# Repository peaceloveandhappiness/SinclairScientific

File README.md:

# Sinclair Scientific

This is a recreation of the original 1974 Scientific Calculator, the first affordable calculator with more than just + - ÷ ×.

Hewlett Packard had released it’s first “scientific” calculator two years earlier, and despite it costing literally as much as a fairly nice used car, it was a very successful product. Texas Instruments, on the other hand, had a widely available “four function” chip that was the heart of every cheap digital calculator, but was limited to adding, subtracting, multiplying and dividing, with limited precision.

Enter Clive Sinclair and Nigel Searle, who figured out how to use the ultra-meager 320 bytes of instruction space on that TI device to implement sine, asin, cos, acos, tan, atan, log, and antilog, in scientific notation! A feat of hacking that’s mystifying even now.

We have recreated this hallowed machine using an emulator of the TI chip, running the original instructions, at the original speed. It has lots of quirks and issues, some of which are described in this manual, some of which we had fun exploring. Far from diminishing it, these idiosyncrasies, in reality, highlight the amazing achievement that this device represents.

Enjoy!

## Inspiration

This work was inspired by and largely based upon [ArduinoEnigma's similar project](https://gitlab.com/arduinoenigma/ArduinoNanoSinclairScientificCalculator), which was inspired by [Ken Shirriff's Sinclair Scientific Calculator Simulator](http://righto.com/sinclair). The hardware design is based upon [Adafruit's Feather M0](https://github.com/adafruit/Adafruit-Feather-M0-Basic-Proto-PCB), as well as [ArduinoEnigma's hardware designs](https://hackaday.io/project/91895-sinclair-scientific-calculator-emulator). The firmware used in this project is based on [ArduinoEnigma's SinclairScientific7 code](https://gitlab.com/arduinoenigma/ArduinoNanoSinclairScientificCalculator/tree/master/SinclairScientific7) and [Adafruit's SAMD toolchain](https://github.com/adafruit/ArduinoCore-samd).

* [Ken Shirriff's Simulator](http://files.righto.com/calculator/sinclair_scientific_simulator.html)
* [ArduinoEnigma's Arduino Code](https://github.com/arduinoenigma/ArduinoNanoSinclairScientificCalculator)
* [ArduinoEnigma's Hackster Guide](https://www.hackster.io/arduinoenigma/sinclair-scientific-calculator-emulator-a11dba)
* [ArduinoEnigma's Hackaday Guide](https://hackaday.io/project/91895-sinclair-scientific-calculator-emulator)
* [ArduinoEnigma's Tindie Page](https://www.tindie.com/products/ArduinoEnigma/sinclair-scientific-calculator-emulator/)
* [Adafruit's Feather M0](https://github.com/adafruit/Adafruit-Feather-M0-Basic-Proto-PCB)

## Credits

* Thank you Joerg Woerner of [Datamath Calculator Museum](www.datamath.org/) for finding and scanning the original [Sinclair Scientific Operating Manual](www.datamath.net/Manuals_Others/Sinclair_Scientific_GB.pdf).
* Thank you [Katherine Wasserman](www.wass.net/) for finding the original [Sinclair Scientific Assembly Manual](www.wass.net/manuals/Sinclair%20Scientific%20Assembly.pdf)
* Thank you [ArduinoEnigma](www.arduinoenigma.blogspot.com) for starting the project and making the previous iterations. Awesome work!
* Thank you [Ken Shirriff](www.righto.com) for your immense talents and hard work, not only on this emulator but on lots of interesting stuff.
* Thank you [Adafruit](www.adafruit.com) for all of your incredible open source work.

## Additional Information

* [Wikipedia Page for the Sinclair Scientific](https://en.wikipedia.org/wiki/Sinclair_Scientific)
* [Historical Info about the Sinclair Scientific](http://rk.nvg.ntnu.no/sinclair/calculators/scientific.htm)
* [Technical Info about the Sinclair Scientific](http://www.vintagecalculators.com/html/scientific_-_giant_scientific.html)
* [Sinclair Scientific Operating Manual](http://www.datamath.net/Manuals_Others/Sinclair_Scientific_GB.pdf)
* [Sinclair Scientific Assembly Manual](http://www.wass.net/manuals/Sinclair%20Scientific%20Assembly.pdf)

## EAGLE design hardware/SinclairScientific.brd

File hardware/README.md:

# Sinclair Scientific Hardware

## Revision History

### v1A

* Initial revision, based on [ArduinoEnigma's design](https://cdn.hackaday.io/files/918953931635680/V5%20Schematic.png)

### v1B

* Replaced Arduino NANO MCU with one used by Adafruit Feather M0 (SAMD21G18)
* Replaced alkaline batteries with LiPo battery
* Added LiPo battery charging circuit
* Changed LED resistor values to work with 3.3V
* Changed 7-segment displays to mount on a daughter board to allow them to be flush mounted with the faceplate
* Swapped existing tactile buttons for ones that can be used with button caps
* Swapped existing ON/OFF switch for more comfortable one
* Added charging LED that can be seen by user
* Moved LED segments [B, E] to [D0, D1] pins to allow button input lines to use [D8, D9] exclusively

### v1C

* Fixed footprint for flash memory IC
* Changed button spacing to match original sinclair dimensions
* Replaced power switch with SMT device

### Future Changes

* Consider using LED or 7-segment display driver
  * [MAX6954](https://www.maximintegrated.com/en/app-notes/index.mvp/id/3210)
  * [MAX6957](https://www.maximintegrated.com/en/products/power/display-power-control/MAX6957.html)
  * [MAX7301](https://www.maximintegrated.com/en/products/interface/controllers-expanders/MAX7301.html)
  * Maxim has many other parts that may work better

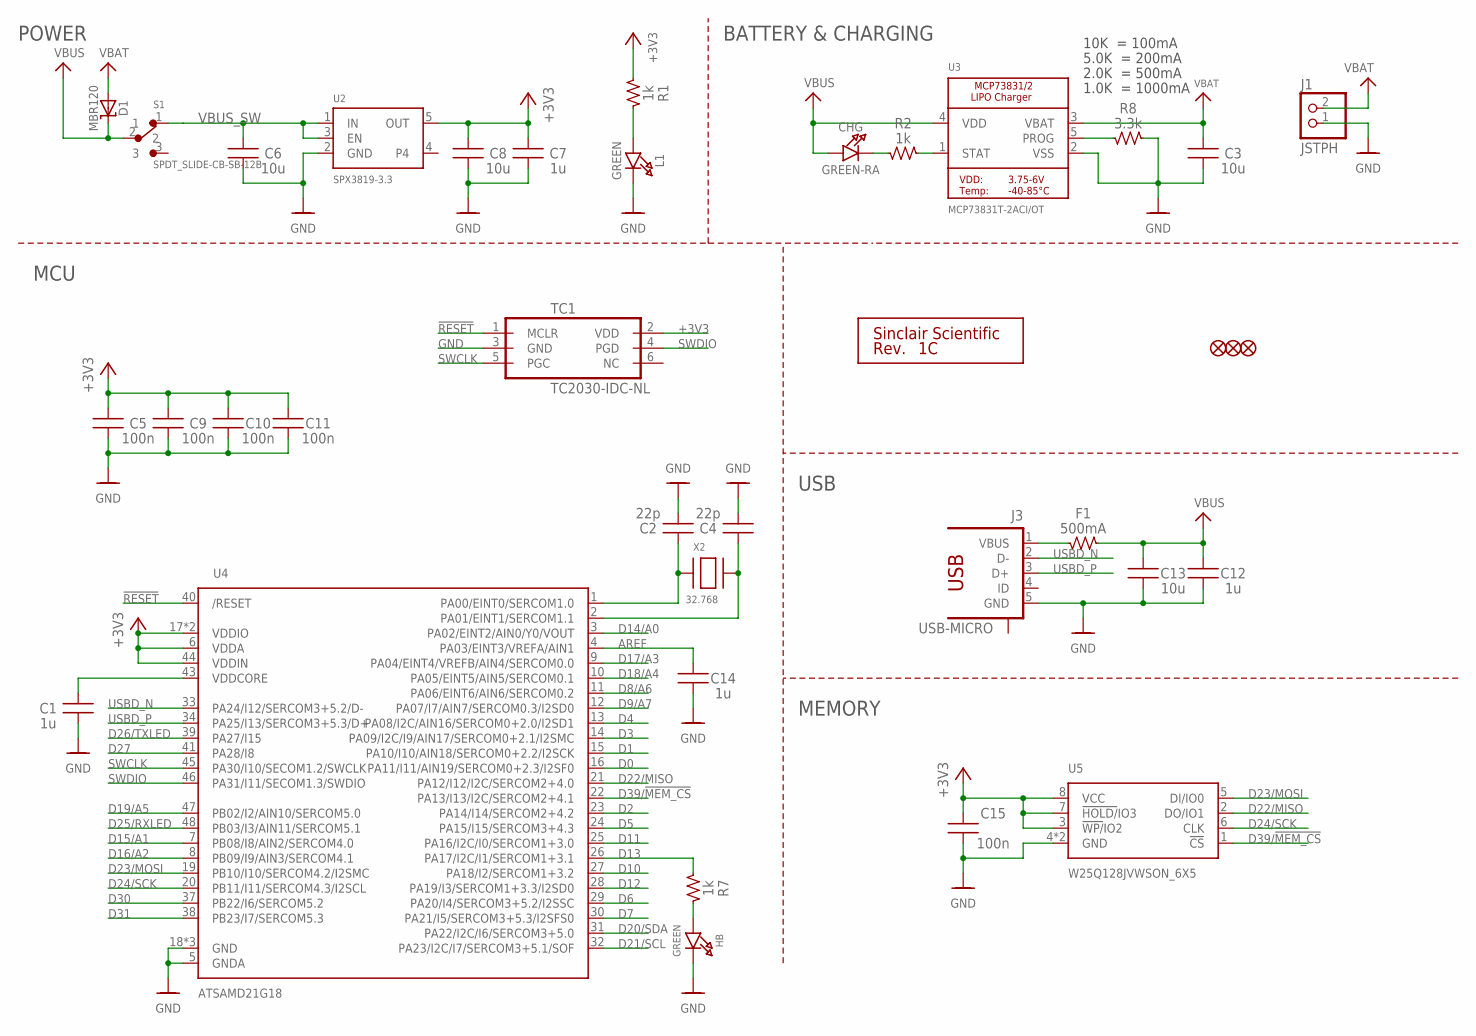
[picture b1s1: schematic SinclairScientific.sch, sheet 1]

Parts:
C1, C7, C12, C14: 1u; C0603; MPN C1608X7R1C105M080AC
C2, C4: 22p; C0603; MPN GQM1875C2E220JB12D
C3, C6, C8, C13: 10u; C0805; MPN GRM21BR61C106KE15K
C5, C9, C10, C11, C15: 100n; C0603; MPN 06035C104K4Z4A
CHG: GREEN-RA; CHIPLED_0805_NOOUTLINE; MPN LTST-S220KGKT
D1: MBR120; SOD-123; MPN MBR120VLSFT1G
F1: 500mA; R0805; MPN 0ZCK0050FF2E
FID1, FID2, FID3: FIDUCIAL""; FIDUCIAL_1MM
HB: GREEN; CHIPLED_0805_NOOUTLINE; MPN LTST-C170GKT
J1: JSTPH; JSTPH2; MPN S2B-PH-SM4-TB(LF)(SN)
J3: USB-MICRO; USB-10118192-0001LF
L1: GREEN; CHIPLED_0805_NOOUTLINE; MPN LTST-C170GKT
R1, R2, R7: 1k; R0603; MPN RC0603FR-071KL
R8: 3.3k; R0603; MPN RC0603FR-073K3L
S1: SPDT_SLIDE-CB-SB-12B; CL-SB-12B; MPN CL-SB-12B-01T
SILK-QC: SILK_QC
TC1: TC2030-IDC-NL
U2: SPX3819-3.3; SOT23-5; MPN SPX3819M5-L-3-3/TR
U3: MCP73831T-2ACI/OT; SOT23-5; MPN MCP73831T-2ACI/OT
U4: ATSAMD21G18; TQFP48_7MM; MPN ATSAMD21G18A-AUT
U5: W25Q128JVWSON_6X5; SON127P600X500X80-9N; MPN W25Q128JVPIM
X2: 32.768; XTAL3215; MPN ECS-.327-12.5-34B-TR

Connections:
!RESET: TC1.1 (MCLR), U4.40 (/RESET)
+3V3: C5.1, C7.1, C8.1, C9.1, C10.1, C11.1, C15.1, R1.1, TC1.2 (VDD), U2.5 (OUT), U4.6 (VDDA), U4.17 (VDDIO), U4.36 (VDDIO), U4.44 (VDDIN), U5.3 (!WP/!IO2), U5.7 (!HOLD/!IO3), U5.8 (VCC); also elsewhere on the board
AREF: C14.1, U4.4 (PA03/EINT3/VREFA/AIN1)
D0: U4.16 (PA11/I11/AIN19/SERCOM0+2.3/I2SF0); also elsewhere on the board
D1: U4.15 (PA10/I10/AIN18/SERCOM0+2.2/I2SCK); also elsewhere on the board
D2: U4.23 (PA14/I14/SERCOM2+4.2); also elsewhere on the board
D3: U4.14 (PA09/I2C/I9/AIN17/SERCOM0+2.1/I2SMC); also elsewhere on the board
D4: U4.13 (PA08/I2C/AIN16/SERCOM0+2.0/I2SD1); also elsewhere on the board
D5: U4.24 (PA15/I15/SERCOM3+4.3); also elsewhere on the board
D6: U4.29 (PA20/I4/SERCOM3+5.2/I2SSC); also elsewhere on the board
D7: U4.30 (PA21/I5/SERCOM3+5.3/I2SFS0); also elsewhere on the board
D8/A6: U4.11 (PA06/EINT6/AIN6/SERCOM0.2); also elsewhere on the board
D9/A7: U4.12 (PA07/I7/AIN7/SERCOM0.3/I2SD0); also elsewhere on the board
D10: U4.27 (PA18/I2/SERCOM1+3.2); also elsewhere on the board
D11: U4.25 (PA16/I2C/I0/SERCOM1+3.0); also elsewhere on the board
D12: U4.28 (PA19/I3/SERCOM1+3.3/I2SD0); also elsewhere on the board
D13: R7.1, U4.26 (PA17/I2C/I1/SERCOM1+3.1)
D14/A0: U4.3 (PA02/EINT2/AIN0/Y0/VOUT); also elsewhere on the board
D15/A1: U4.7 (PB08/I8/AIN2/SERCOM4.0); also elsewhere on the board
D16/A2: U4.8 (PB09/I9/AIN3/SERCOM4.1); also elsewhere on the board
D17/A3: U4.9 (PA04/EINT4/VREFB/AIN4/SERCOM0.0); also elsewhere on the board
D18/A4: U4.10 (PA05/EINT5/AIN5/SERCOM0.1); also elsewhere on the board
D19/A5: U4.47 (PB02/I2/AIN10/SERCOM5.0); also elsewhere on the board
D20/SDA: U4.31 (PA22/I2C/I6/SERCOM3+5.0)
D21/SCL: U4.32 (PA23/I2C/I7/SERCOM3+5.1/SOF)
D22/MISO: U4.21 (PA12/I12/I2C/SERCOM2+4.0), U5.2 (DO/IO1)
D23/MOSI: U4.19 (PB10/I10/SERCOM4.2/I2SMC), U5.5 (DI/IO0)
D24/SCK: U4.20 (PB11/I11/SERCOM4.3/I2SCL), U5.6 (CLK)
D25/RXLED: U4.48 (PB03/I3/AIN11/SERCOM5.1)
D26/TXLED: U4.39 (PA27/I15)
D27: U4.41 (PA28/I8)
D30: U4.37 (PB22/I6/SERCOM5.2)
D31: U4.38 (PB23/I7/SERCOM5.3)
D39/!MEM_CS: U4.22 (PA13/I13/I2C/SERCOM2+4.1), U5.1 (!CS)
EXTAL32: C2.1, U4.1 (PA00/EINT0/SERCOM1.0), X2.P$1
GND: C1.2, C2.2, C3.2, C4.2, C5.2, C6.2, C7.2, C8.2, C9.2, C10.2, C11.2, C12.2, C13.2, C14.2, C15.2, HB.C, J1.1, J3.5 (GND), L1.C, R8.2, TC1.3 (GND), U2.2 (GND), U3.2 (VSS), U4.5 (GNDA), U4.18 (GND), U4.35 (GND), U4.42 (GND), U5.4 (GND), U5.9 (GND); also elsewhere on the board
unnamed: CHG.C, R2.1
unnamed: HB.A, R7.2
unnamed: R2.2, U3.1 (STAT)
unnamed: R8.1, U3.5 (PROG)
unnamed: L1.A, R1.2
unnamed: F1.1, J3.1 (VBUS)
SWCLK: TC1.5 (PGC), U4.45 (PA30/I10/SECOM1.2/SWCLK)
SWDIO: TC1.4 (PGD), U4.46 (PA31/I11/SECOM1.3/SWDIO)
USBD_N: J3.2 (D-), U4.33 (PA24/I12/SERCOM3+5.2/D-)
USBD_P: J3.3 (D+), U4.34 (PA25/I13/SERCOM3+5.3/D+)
VBAT: C3.1, D1.A, J1.2, U3.3 (VBAT)
VBUS: C12.1, C13.1, CHG.A, D1.C, F1.2, S1.2, U3.4 (VDD)
VBUS_SW: C6.1, S1.1, U2.1 (IN), U2.3 (EN)
VDDCORE: C1.1, U4.43 (VDDCORE)
XTAL32: C4.1, U4.2 (PA01/EINT1/SERCOM1.1), X2.P$2

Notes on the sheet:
POWER
10K = 100mA
5.0K = 200mA
2.0K = 500mA
1.0K = 1000mA
BATTERY & CHARGING
USB
MCU
MEMORY

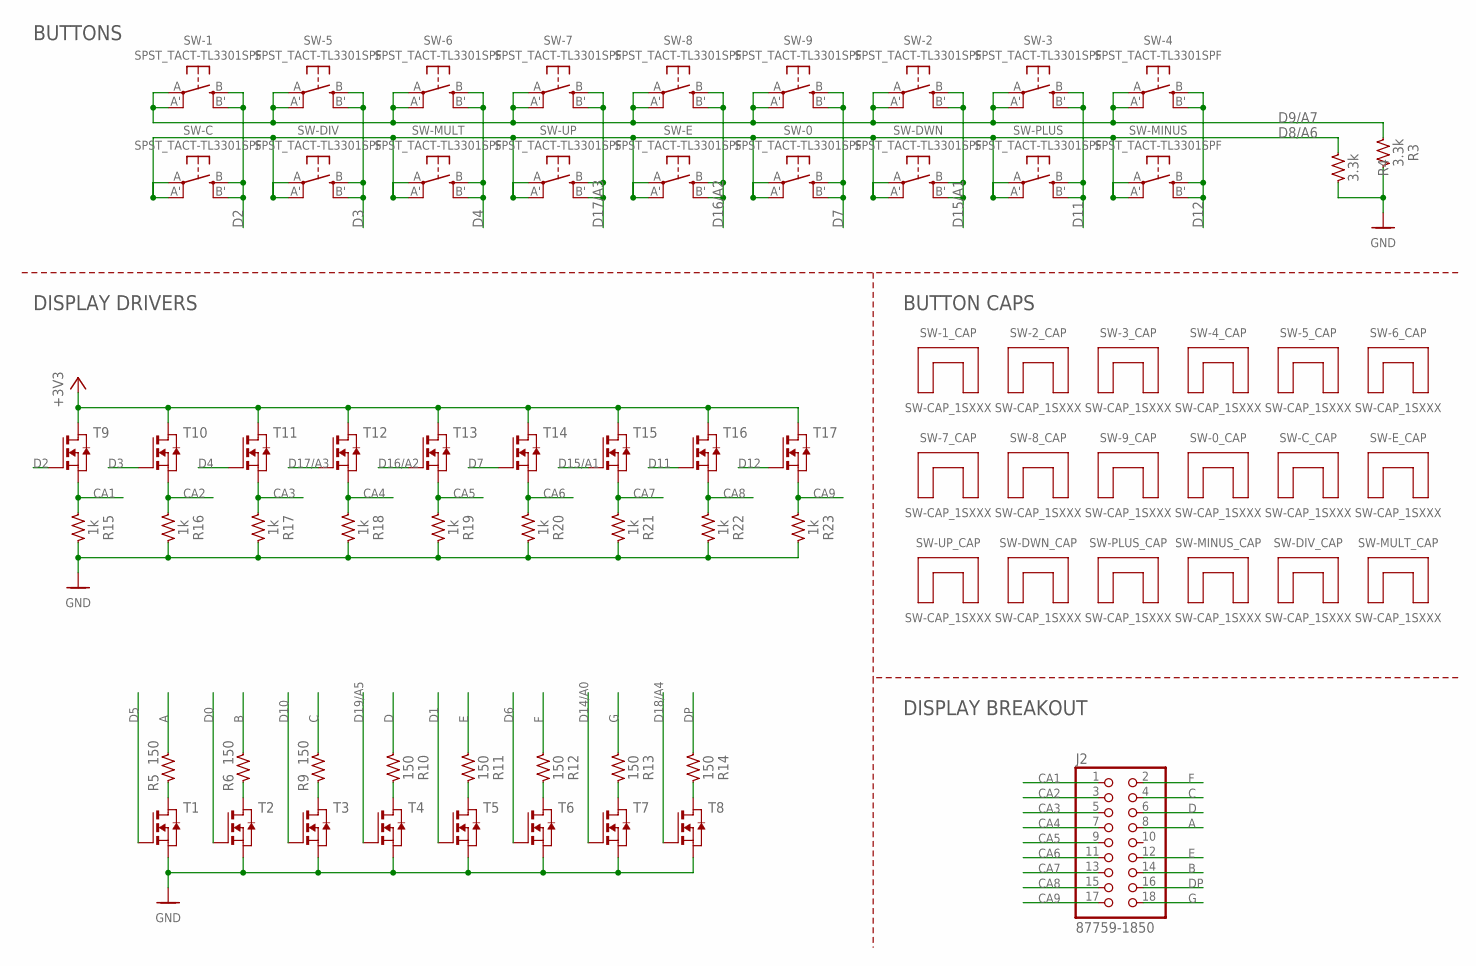
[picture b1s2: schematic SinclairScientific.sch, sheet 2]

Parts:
J2: 87759-1850; 2X09-2MM-SMD; MPN 87759-1850
R3, R4: 3.3k; R0603; MPN RC0603FR-073K3L
R5, R6, R9, R10, R11, R12, R13, R14: 150; R0603; MPN RC0603FR-07150RL
R15, R16, R17, R18, R19, R20, R21, R22, R23: 1k; R0603; MPN RC0603FR-071KL
SW-0, SW-2, SW-3, SW-4, SW-5, SW-6, SW-7, SW-8, SW-9: SPST_TACT-TL3301SPF; TACT_6X6
SW-0_CAP, SW-1_CAP, SW-2_CAP, SW-3_CAP, SW-4_CAP, SW-5_CAP, SW-6_CAP, SW-7_CAP, SW-8_CAP, SW-9_CAP: SW-CAP_1SXXX; SW-CAP_1SWXXX
SW-1: SPST_TACT-TL3301SPF; TACT_6X6; MPN TL3301SPF260QG
SW-C: SPST_TACT-TL3301SPF; TACT_6X6
SW-C_CAP: SW-CAP_1SXXX; SW-CAP_1SWXXX
SW-DIV: SPST_TACT-TL3301SPF; TACT_6X6
SW-DIV_CAP: SW-CAP_1SXXX; SW-CAP_1SWXXX
SW-DWN: SPST_TACT-TL3301SPF; TACT_6X6
SW-DWN_CAP: SW-CAP_1SXXX; SW-CAP_1SWXXX
SW-E: SPST_TACT-TL3301SPF; TACT_6X6
SW-E_CAP: SW-CAP_1SXXX; SW-CAP_1SWXXX
SW-MINUS: SPST_TACT-TL3301SPF; TACT_6X6
SW-MINUS_CAP: SW-CAP_1SXXX; SW-CAP_1SWXXX
SW-MULT: SPST_TACT-TL3301SPF; TACT_6X6
SW-MULT_CAP: SW-CAP_1SXXX; SW-CAP_1SWXXX
SW-PLUS: SPST_TACT-TL3301SPF; TACT_6X6
SW-PLUS_CAP: SW-CAP_1SXXX; SW-CAP_1SWXXX
SW-UP: SPST_TACT-TL3301SPF; TACT_6X6
SW-UP_CAP: SW-CAP_1SXXX; SW-CAP_1SWXXX
T1, T2, T3, T4, T5, T6, T7, T8, T10, T11, T12, T13, T14, T15, T16, T17: NMOSSOT23-FDV303N; SOT-23
T9: NMOSSOT23-FDV303N; SOT-23; MPN FDV303N

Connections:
+3V3: T9.1 (D), T10.1 (D), T11.1 (D), T12.1 (D), T13.1 (D), T14.1 (D), T15.1 (D), T16.1 (D), T17.1 (D); also elsewhere on the board
A: J2.8, R5.1
B: J2.14, R6.1
C: J2.4, R9.1
CA1: J2.1, R15.1, T9.2 (S)
CA2: J2.3, R16.1, T10.2 (S)
CA3: J2.5, R17.1, T11.2 (S)
CA4: J2.7, R18.1, T12.2 (S)
CA5: J2.9, R19.1, T13.2 (S)
CA6: J2.11, R20.1, T14.2 (S)
CA7: J2.13, R21.1, T15.2 (S)
CA8: J2.15, R22.1, T16.2 (S)
CA9: J2.17, R23.1, T17.2 (S)
D: J2.6, R10.1
D0: T2.3 (G); also elsewhere on the board
D1: T5.3 (G); also elsewhere on the board
D2: SW-1.B (S), SW-1.B' (S1), SW-C.B (S), SW-C.B' (S1), T9.3 (G); also elsewhere on the board
D3: SW-5.B (S), SW-5.B' (S1), SW-DIV.B (S), SW-DIV.B' (S1), T10.3 (G); also elsewhere on the board
D4: SW-6.B (S), SW-6.B' (S1), SW-MULT.B (S), SW-MULT.B' (S1), T11.3 (G); also elsewhere on the board
D5: T1.3 (G); also elsewhere on the board
D6: T6.3 (G); also elsewhere on the board
D7: SW-0.B (S), SW-0.B' (S1), SW-9.B (S), SW-9.B' (S1), T14.3 (G); also elsewhere on the board
D8/A6: R4.1, SW-0.A, SW-0.A' (P1), SW-C.A, SW-C.A' (P1), SW-DIV.A, SW-DIV.A' (P1), SW-DWN.A, SW-DWN.A' (P1), SW-E.A, SW-E.A' (P1), SW-MINUS.A, SW-MINUS.A' (P1), SW-MULT.A, SW-MULT.A' (P1), SW-PLUS.A, SW-PLUS.A' (P1), SW-UP.A, SW-UP.A' (P1); also elsewhere on the board
D9/A7: R3.1, SW-1.A, SW-1.A' (P1), SW-2.A, SW-2.A' (P1), SW-3.A, SW-3.A' (P1), SW-4.A, SW-4.A' (P1), SW-5.A, SW-5.A' (P1), SW-6.A, SW-6.A' (P1), SW-7.A, SW-7.A' (P1), SW-8.A, SW-8.A' (P1), SW-9.A, SW-9.A' (P1); also elsewhere on the board
D10: T3.3 (G); also elsewhere on the board
D11: SW-3.B (S), SW-3.B' (S1), SW-PLUS.B (S), SW-PLUS.B' (S1), T16.3 (G); also elsewhere on the board
D12: SW-4.B (S), SW-4.B' (S1), SW-MINUS.B (S), SW-MINUS.B' (S1), T17.3 (G); also elsewhere on the board
D14/A0: T7.3 (G); also elsewhere on the board
D15/A1: SW-2.B (S), SW-2.B' (S1), SW-DWN.B (S), SW-DWN.B' (S1), T15.3 (G); also elsewhere on the board
D16/A2: SW-8.B (S), SW-8.B' (S1), SW-E.B (S), SW-E.B' (S1), T13.3 (G); also elsewhere on the board
D17/A3: SW-7.B (S), SW-7.B' (S1), SW-UP.B (S), SW-UP.B' (S1), T12.3 (G); also elsewhere on the board
D18/A4: T8.3 (G); also elsewhere on the board
D19/A5: T4.3 (G); also elsewhere on the board
DP: J2.16, R14.1
E: J2.12, R11.1
F: J2.2, R12.1
G: J2.18, R13.1
GND: R3.2, R4.2, R15.2, R16.2, R17.2, R18.2, R19.2, R20.2, R21.2, R22.2, R23.2, T1.2 (S), T2.2 (S), T3.2 (S), T4.2 (S), T5.2 (S), T6.2 (S), T7.2 (S), T8.2 (S); also elsewhere on the board
unnamed: R5.2, T1.1 (D)
unnamed: R6.2, T2.1 (D)
unnamed: R9.2, T3.1 (D)
unnamed: R10.2, T4.1 (D)
unnamed: R11.2, T5.1 (D)
unnamed: R12.2, T6.1 (D)
unnamed: R13.2, T7.1 (D)
unnamed: R14.2, T8.1 (D)

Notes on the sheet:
BUTTONS
DISPLAY DRIVERS
DISPLAY BREAKOUT
BUTTON CAPS

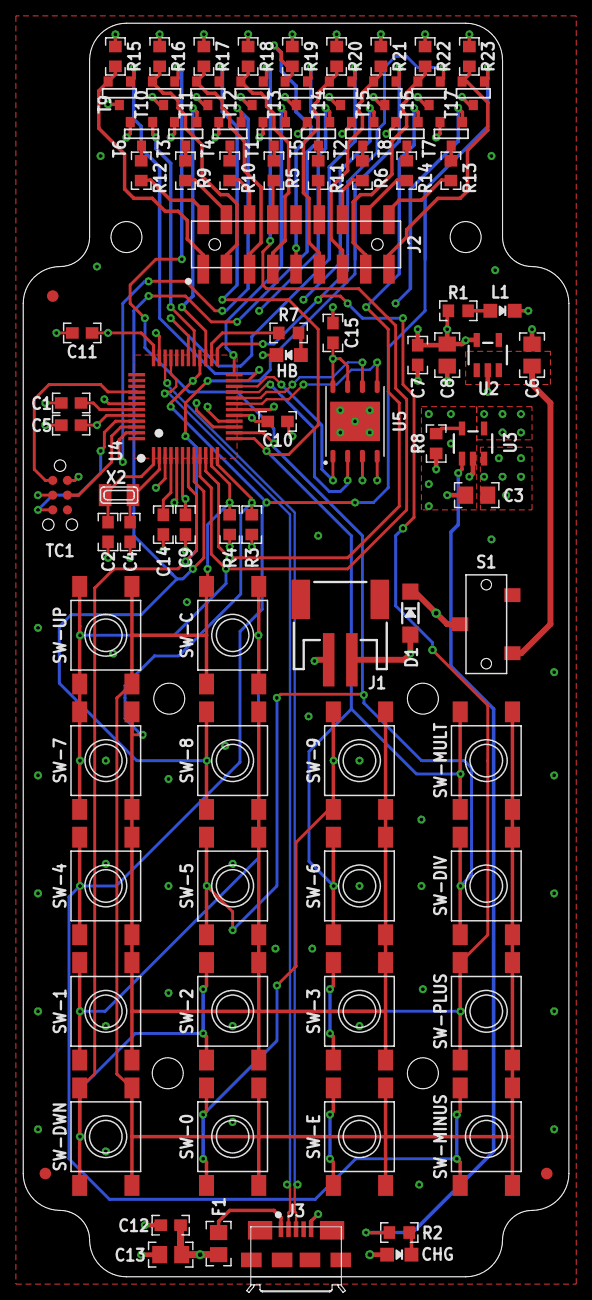
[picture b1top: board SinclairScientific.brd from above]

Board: 4 copper layers, 47.0 x 108.0 mm, 117 parts (2 on the bottom side), 69 nets.

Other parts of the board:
U$17: LOGO_PLH_2700
U$50, U$51, U$52, U$53, U$54, U$55: HOLE_3-48

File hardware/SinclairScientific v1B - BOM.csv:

Qty,DNP,Value,Parts,MFG,MPN,PN-DK,Device,Package,Description,
2,,22pF,"C2, C4",Murata Electronics North America,GQM1875C2E220JB12D,490-16699-1-ND,C-USC0603,C0603,CAP CER 22PF 250V NP0 0603,
5,,100n,"C9, C10, C11, C5, C15",AVX Corporation,06035C104K4Z4A,478-10679-1-ND,C-USC0603,C0603,CAP CER 0.1UF 50V X7R 0603,
4,,1uF,"C1, C7, C12, C14",TDK Corporation,C1608X7R1C105M080AC,445-5131-1-ND,C-USC0603,C0603,CAP CER 1UF 16V X7R 0603,
4,,10uF,"C3, C6, C8, C13",Murata Electronics North America,GRM21BR61C106KE15K,490-6473-1-ND,C-USC0805,C0805,CAP CER 10UF 16V X5R 0805,
8,,150,"R5, R6, R9, R10, R11, R12, R13, R14",Yageo,RC0603FR-07150RL,311-150HRCT-ND,R-US_R0603,R0603,RES SMD 150 OHM 1% 1/10W 0603,
12,,1k,"R1, R2, R7, R15, R16, R17, R18, R19, R20, R21, R22, R23",Yageo,RC0603FR-071KL,311-1.00KHRCT-ND,R-US_R0603,R0603,RES SMD 1K OHM 1% 1/10W 0603,
3,,3.3k,"R3, R4, R8",Yageo,RC0603FR-073K3L,311-3.30KHRCT-ND,R-US_R0603,R0603,RES SMD 3.3K OHM 1% 1/10W 0603,
1,,500mA,F1,Bel Fuse Inc.,0ZCK0050FF2E,507-1813-1-ND,R-US_R0805,R0805,PTC RESET FUSE 6V 500MA 0805,
1,,MBR120,D1,ON Semiconductor,MBR120VLSFT1G,MBR120VLSFT1GOSCT-ND,DIODE-SCHOTTKYSOD-123,SOD-123,DIODE SCHOTTKY 20V 1A SOD123FL,
2,,Green,"HB, L1",Lite-On Inc.,LTST-C170GKT,160-1179-1-ND,LED0805_NOOUTLINE,CHIPLED_0805_NOOUTLINE,LED GREEN CLEAR SMD,
1,,Green,CHG,Lite-On Inc.,LTST-S220KGKT,160-1468-1-ND,LED0805_NOOUTLINE,CHIPLED_0805_NOOUTLINE,LED GREEN CLEAR CHIP SMD R/A,
1,,32.768,X2,ECS Inc.,ECS-.327-12.5-34B-TR,XC1617CT-ND,XTAL-3.2X1.5,XTAL3215,CRYSTAL 32.7680KHZ 12.5PF SMD,
17,,,"T1, T2, T3, T4, T5, T6, T7, T8, T9, T10, T11, T12, T13, T14, T15, T16, T17",ON Semiconductor,FDV303N,FDV303NCT-ND,NMOSSOT23,SOT-23,MOSFET N-CH 25V 680MA SOT-23,x
1,,SPST_SLIDE,S1,Nidec Copal Electronics,CL-SB-12B-01T,563-1318-1-ND,SPST_SLIDE,SPST_SLIDE-CL-SB-12B,SWITCH SLIDE SPDT 200MA 12V,
18,,SPST_TACT-6X6,"SW-0, SW-1, SW-2, SW-3, SW-4, SW-5, SW-6, SW-7, SW-8, SW-9, SW-C, SW-DIV, SW-DWN, SW-E, SW-MINUS, SW-MULT, SW-PLUS, SW-UP",E-Switch,TL3301SPF260QG,EG1870CT-ND,SPST_TACT-6X6,TACT_6X6,SWITCH TACTILE SPST-NO 0.05A 12V,
1,,SPX3819-3.3,U2,"MaxLinear, Inc.",SPX3819M5-L-3-3/TR,1016-1873-1-ND,VREG_SOT23-5,SOT23-5,IC REG LINEAR 3.3V 500MA SOT23-5,
1,,MCP73831T-2ACI/OT,U3,Microchip Technology,MCP73831T-2ACI/OT,MCP73831T-2ACI/OTCT-ND,MCP73831/2,SOT23-5,IC CONTROLLR LI-ION 4.2V SOT23-5,
1,,W25Q128JVSO,U5,Winbond Electronics,W25Q128JVPIM,W25Q128JVPIMCT-ND,W25Q128JVSO,SON127P800X600X80-9N,IC FLASH 128M SPI 133MHZ 8WSON,
1,,ATSAMD21G18,U4,Microchip Technology,ATSAMD21G18A,ATSAMD21G18A-AFTCT-ND,ATSAMD21J_QFP,TQFP48_7MM,IC MCU 32BIT 256KB FLASH 48TQFP,
1,,USB-MICRO,J3,Amphenol,10118192-0001LF,609-4613-1-ND,USB-MICRO,USB-10118192-0001LF,CONN USB MICRO B RECPT SMT R/A,
1,,JSTPH,J1,JST Sales America Inc.,S2B-PH-SM4-TB(LF)(SN),455-1749-1-ND,CON_JST_PH_2PIN,JSTPH2,CONN HEADER PH SIDE 2POS 2MM SMD,
1,,,J2,Molex Connector Corporation,87759-1850,WM18656-ND ,PINHD-2X9-2MM-SMD,2X09-2MM-SMD,CONN HEADER 18POS 2MM VERT SMD,
1,DNP,TC2030-IDC-NL,TC1,Tag-Connect,TC2030-IDC,,TC2030-IDC-NL,TC2030-IDC-NL,Tag-Connect In Circuit Programming & Debug Cable 6 Pin,

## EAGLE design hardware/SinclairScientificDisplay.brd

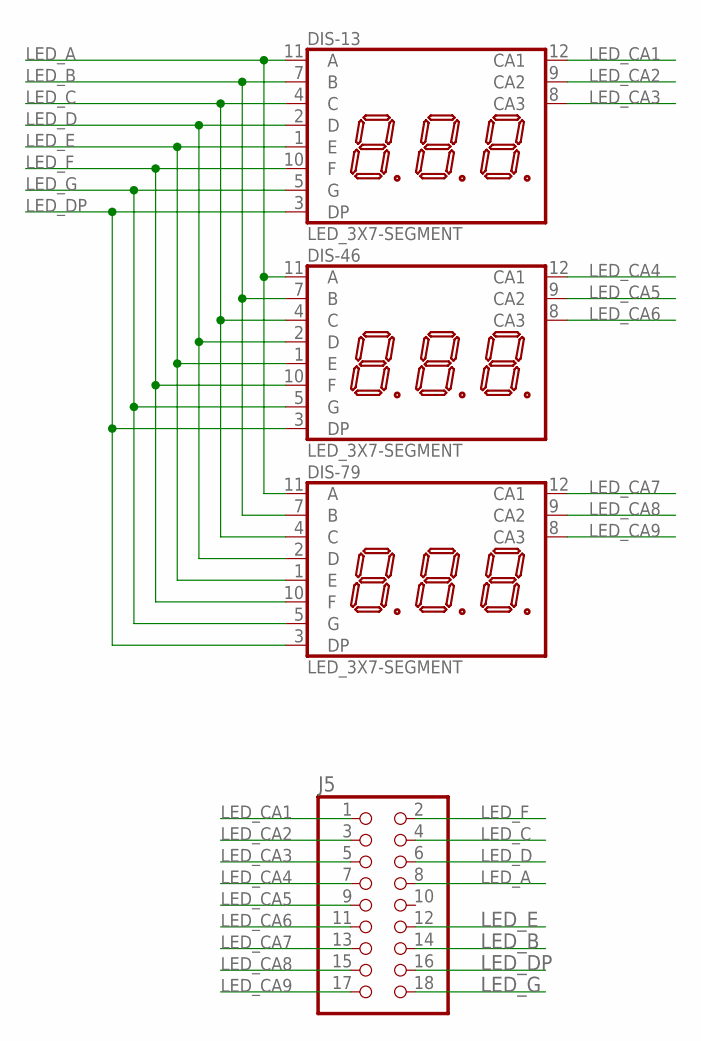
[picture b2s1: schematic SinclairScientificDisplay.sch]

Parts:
DIS-13, DIS-46, DIS-79: LED_3X7-SEGMENT; 2352B
J5: PINHD-2X9-2MM; 2X09-2MM

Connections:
LED_A: DIS-13.11 (A), DIS-46.11 (A), DIS-79.11 (A), J5.8
LED_B: DIS-13.7 (B), DIS-46.7 (B), DIS-79.7 (B), J5.14
LED_C: DIS-13.4 (C), DIS-46.4 (C), DIS-79.4 (C), J5.4
LED_CA1: DIS-13.12 (CA1), J5.1
LED_CA2: DIS-13.9 (CA2), J5.3
LED_CA3: DIS-13.8 (CA3), J5.5
LED_CA4: DIS-46.12 (CA1), J5.7
LED_CA5: DIS-46.9 (CA2), J5.9
LED_CA6: DIS-46.8 (CA3), J5.11
LED_CA7: DIS-79.12 (CA1), J5.13
LED_CA8: DIS-79.9 (CA2), J5.15
LED_CA9: DIS-79.8 (CA3), J5.17
LED_D: DIS-13.2 (D), DIS-46.2 (D), DIS-79.2 (D), J5.6
LED_DP: DIS-13.3 (DP), DIS-46.3 (DP), DIS-79.3 (DP), J5.16
LED_E: DIS-13.1 (E), DIS-46.1 (E), DIS-79.1 (E), J5.12
LED_F: DIS-13.10 (F), DIS-46.10 (F), DIS-79.10 (F), J5.2
LED_G: DIS-13.5 (G), DIS-46.5 (G), DIS-79.5 (G), J5.18

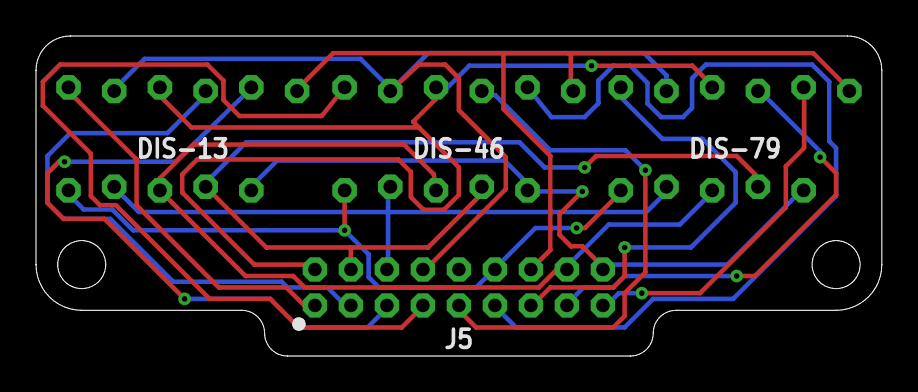
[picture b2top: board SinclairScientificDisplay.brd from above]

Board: 2 copper layers, 47.0 x 17.8 mm, 6 parts (0 on the bottom side), 17 nets.

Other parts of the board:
U$1, U$2: HOLE_3-48

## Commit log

2018-10-04 Initial commit. Started making hardware changes.
2018-10-07 Added more to schematic, started PCB placement, still WIP
2018-10-18 Schematic nearly finalized, still working on board dimensions and component placement
2018-10-23 Moved displays to their own sch/brd files, nearly finished routing main board
2018-10-23 Finished routing
2018-10-23 Added some silkscreen labels and logo
2018-10-23 Copied SinclairScientific7 version of code into repo, no changes made
2018-11-03 Modified firmware to match changes to hardware.
2018-11-03 Fixed some hardware issues found in testing v1B prototype
2018-11-05 Converted local library to managed library. Fixed more hardware issues found from testing v1B prototype.
2018-11-07 Changed on/off switch to SMD type, fixed some DFM issues
2018-11-07 Changed button spacing, finalized rev 1C layouts
2018-11-09 Updated BOM and added BOM attributes to schematic
2018-11-12 Finalized top layer of faceplate board
2018-11-22 Increased coverplate silkscreen text width
2018-11-22 Added manuals and images
2018-11-22 Added STEP files for each board
2018-11-22 Added artwork used to create faceplate PCB silkscreen text
2018-12-01 Updated firmware to prevent LED drive pins from being Hi-Z on startup, which can cause LEDs to be on
2018-12-01 Added toolchain files (modified version of Adafruit's SAMD library)
2018-12-01 Added PDFs of schematics for easier reference
2018-12-08 Updated credits
2018-12-14 Updated readme text and added print version of manual.

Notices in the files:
hardware/SinclairScientific.sch:
LICENSE: CC-BY-SA
